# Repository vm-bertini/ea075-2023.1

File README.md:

# EA075 - Introdução a Projeto de Sistemas Embarcados

1° Semestre de 2023

Profa. Paula Dornhofer Paro Costa

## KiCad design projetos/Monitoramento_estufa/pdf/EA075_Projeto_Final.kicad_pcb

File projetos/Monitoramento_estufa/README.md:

# `<Monitoramento_Estufa>`
# `<Greenhouse_monitoring>`

## Apresentação

O presente projeto foi originado no contexto das atividades da disciplina de graduação *EA075 - Sistemas Embarcados*, 
oferecida no primeiro semestre de 2023, na Unicamp, sob supervisão da Profa. Dra. Paula Dornhofer Paro Costa, do Departamento de Engenharia de Computação e Automação (DCA) da Faculdade de Engenharia Elétrica e de Computação (FEEC).

> |Nome  | RA | Curso|
> |--|--|--|
> | Felipe Souza Sisnando de Araujo  | 239617  | Eng. Elétrica|
> | Levi Santos Volotão  | 239783  | Eng. Elétrica|

## Descrição do Projeto
> 
> Hoje em dia, observa-se o surgimento de cada vez mais estufas controladas, pois são um ambiente controlado em que plantações podem ser monitoradas e os aspectos físicos do ambiente podem ser configurados e otimizados para o crescimento e desenvolvimento adequado de uma certa espécie. Embora o custo inicial de uma estufa seja elevado, ela possibilita uma melhora na qualidade dos produtos, aumentando seu valor agregado, e uma dependência menor de características que não podemos controlar quando cultivadas a céu aberto.
> 
> Com uma plantação em estufa, os parâmetros externos não terão tanta influência, e as épocas do ano influenciarão menos as colheitas, garantindo a produção durante o ano todo, reduzindo fenômenos como falta de abastecimento em determinados períodos do ano e prejuízos econômicos dos cultivadores devido ao clima. Como exemplo, observa-se que "no verão, as chuvas demasiadas danificam as plantas e criam condições favoráveis para o aparecimento de doenças, atrapalhando a produção, sendo a época de maiores preços dos produtos hortícolas pela falta de oferta para abastecimento. Por outro lado, o frio e os ventos, do inverno prolongam o ciclo dessas culturas, que consequentemente desprogramam a produção e causam grandes prejuízos econômicos" [Miura, 2011]. Porém, mesmo com influências externas reduzidas, ainda é necessário o controle interno, devido a problemas como a alta irradiação externa resultando em um efeito de aquecimento dentro da estufa,podendo ser prejudicial à plantação caso não ocorra o controle da temperatura necessário. "Além disso, a alta umidade relativa do ar favorece o aparecimento de doenças e provoca menor desenvolvimento das plantas devido ao fato da planta transpirar menos e ter uma menor absorção de nutrientes nessas condições, enquanto, a baixa umidade relativa do ar juntamente com altas temperaturas provoca o aumento da transpiração, fechamento dos estômatos, redução da taxa de transpiração e abortamento das flores devido a uma polinização deficiente" [Lopes e Stripari, 1997]. 
>
> Desse modo, nós propomos o desenvolvimento de um sistema embarcado responsável pelo monitoramento da estufa, que será capaz de identificar quando os valores de temperatura, umidade e luminosidade estiverem fora da faixa desejada, e será capaz de corrigir esses valores, utilizando sistemas de aquecimento e refrigeração (coolers), sistema de ventilação, aspersores de água e um sistema que controla as lâmpadas responsáveis pela luminosidade da estufa, bem como a luminosidade que entra do ambiente externo, a partir de um "shade" (funciona como uma "cortina") cuja abertura é controlada. Esse monitoramento será de grande utilidade para cultivadores de diversos produtos, visto que as faixas de temperautra, luminosidade e umidade desejadas podem ser configuradas conforme os parâmetros adequados para cada espécie. A instalação desse sistema irá aumentar o valor agregado dos seus produtos, viabilizar o cultivo em todas as épocas do ano e permitir um controle automatizado, sem necessidade de mão de obra.
>  

## Descrição Funcional

### Funcionalidades
>O nosso sistema embarcado será capaz de obter a temperatura do ambiente, a luminosidade e a umidade do ar a partir de sensores. Ele mostrará esses valores em um LCD (Liquid Crystal Display). Inicialmente ele amostrará os valores de temperatura e umidade a cada 10 minutos e a luminosidade a cada 5 minutos, porém esses parâmetros serão configuráveis, e a frequência de amostragem de cada fator pode ser alterada conforme a necessidade do cliente. O sistema também será capaz de detectar quando um valor estiver fora da faixa adequada configurada, e para esse caso, irá iniciar rotinas de tratamento adequadas, controlando o funcionamento dos aspersores de água, sistema de aquecimento, coolers, lâmpadas e "shade".
>
> O sistema poderá : 
> - Ligar e desligar os aspersores de água
>
> - Ligar, desligar e controlar a temperatura do sistema de aquecimento
>
> - Ligar, desligar e controlar a temperatura dos coolers
> 
> - Movimentar o "shade" : Abrir o shade caso a luminosidade esteja abaixo da desejada e fechar o shade caso esteja acima da desejada
>
> - Ligar, desligar e controlar a intensidade da luz das lâmpadas de LED (as lâmpadas serão utilizadas caso a luminosidade não seja o bastante mesmo com o shade totalmente aberto (por exemplo à noite)).

### Configurabilidade
> A estufa está sendo projetada para uma diversidade de espécies de plantas, e cada planta tem suas especificidades em relação ao ambiente para ter uma produtividade melhor. Portanto, será possível configurar a faixa de valores desejada e a frequência com que os dados serão amostrados. Essa configuração será feita por botões. O LCD no modo exibição mostrará o último estado amostrado, e atualizará a cada amostragem. Ao apertar o botão de configuração, o sistema irá funcionar no modo de configuração, e o LCD mostrará os valores definidos para o período de amostragem e os valores máximo e mínimo para cada parâmetro. Para mudar esses valores, haverá 3 botões (além do botão que muda entre o modo de exibição e configuração, totalizando 4 botões), um botão que muda a característica cujo valor deseja-se alterar, um botão para incrementar esse valor e um botão para decrementar esse valor. Ao pressionar o botão de configuração novamente, retorna-se para o modo de exibição. Os valores possíveis para as características obedecerão a limites de acordo com as especificações dos sensores, e o período de amostragem poderá variar de 1 a 59 minutos.
### Eventos
>  O sistema deve tratar os seguintes eventos periódicos:
>
> - Amostragem de temperatura: De X em X minutos deve-se obter o valor da temperatura lido no sensor (em que X é um valor configurável, inicialmete colocado como 10 minutos) 
>
> - Amostragem de umidade: De Y em Y minutos deve-se obter o valor da umidade lido no sensor (em que Y é um valor configurável, inicialmete colocado como 10 minutos) 
>
> - Amostragem de luminosidade: De Z em Z minutos deve-se obter o valor da umidade lido no sensor (em que Z é um valor configurável, inicialmete colocado como 10 minutos)
>
> O sistema deve tratar os seguintes eventos não periódicos:
> 
> - Temperatura dentro da faixa desejada
> 
> - Temperatura abaixo da temperatura mínima configurada
>
> - Temperatura acima da temperatura máxima configurada
>
> - Umidade dentro da faixa desejada
> 
> - Umidade abaixo da umidade mínima configurada
>
> - Umidade acima da umidade máxima configurada
>
> - Luminosidade dentro da faixa desejada
> 
> - Luminosidade abaixo da luminosidade mínima configurada
>
> - Luminosidade acima da luminosidade máxima configurada
>
> - Botão para mudar para o modo configuração apertado
>
> - Botão para incrementar em 1 o valor do parâmetro selecionado apertado
>
> - Botão para decrementar em 1 o valor do parâmetro selecionado apertado
>
> - Botão para mudar parâmetro selecionado (cujo valor deseja-se mudar) apertado
>
>

### Tratamento de Eventos
>
> - Tratamento da amostragem de temperatura: 
> 
> Obter o valor da temperatura e analisar se está acima, abaixo ou dentro da faixa desejada, acionando o tratamento do evento correspondente. 
> 
> - Tratamento da amostragem de umidade:
> 
> Obter o valor da umidade e analisar se está acima, abaixo ou dentro da faixa desejada, acionando o tratamento do evento correspondente. 
> 
> - Tratamento da amostragem de luminosidade: 
> 
>  Obter o valor da luminosidade e analisar se está acima, abaixo ou dentro da faixa desejada, acionando o tratamento do evento correspondente. 
>  
> - Tratamendo quando a temperatura está dentro da faixa desejada:
> 
> O sistema retorna ao fluxo normal do programa
> 
> - Tratamento quando a temperatura está abaixo da temperatura mínima configurada:
> 
> Caso o cooler esteja ligado, desliga o cooler.
> 
>  Caso contrário, se o sistema de aquecimento estiver desligado, liga-se o sistema de aquecimento. Se estiver ligado, aumenta em 5°C a temperatura do aquecedor.
> 
> - Tratamento quando a temperatura está acima da temperatura máxima configurada:
> 
> Caso o aquecedor esteja ligado, desliga o aquecedor. 
> 
> Caso contrário, se o cooler estiver desligado, liga-se o cooler. Se estiver ligado, diminui em 5°C a temperatura do cooler.
> 
> - Tratamento quando a umidade está dentro da faixa desejada:
> 
> O sistema retorna ao fluxo normal do programa
> 
> - Tratamento quando a umidade está abaixo da umidade mínima configurada:
> 
> Caso a ventilação esteja ligada, desliga a ventilação. 
> 
> Caso contrário, liga-se o aspersor de água e, após 30 segundos, ele é desligado.
>
> - Tratamento quando a umidade está acima da umidade máxima configurada:
> 
> Liga-se o sistema de ventilação. 
> 
> Caso já esteja ligado, aumenta sua potência.
>
> - Tratamento quando a luminosidade está dentro da faixa desejada:
> 
> O sistema retorna ao fluxo normal do programa
> 
> - Tratamento quando a luminosidade está abaixo da luminosidade mínima configurada:
> 
> Caso o shade esteja fechado, abrir o shade.
> 
>  Caso contrário, acender as lâmpadas de LED. Se estiverem acesas, aumentar intensidade da luz.
>
> - Tratamento quando a luminosidade está acima da luminosidade máxima configurada:
> 
> Caso as lâmpadas estejam ligadas, desligar as lâmpadas.
> 
>  Caso contrário, fechar o shade
>
> - Tratamento quando o botão de configuração está apertado:
> 
> Caso esteja no modo exibição, muda para o modo de configuração (o LCD passa a mostrar os limites dos parâmetros e o período de amostragem)
> 
> Caso esteja no modo de configuração, muda para o modo exibição(o LCD mostra os valores de temperatura, luminosidade e umidade lidos pelos sensores), estabelece os novos valores limites das faixas de temperatura, umidade e luminosidade e estabelece o novo período de amostragem.
>
> - Tratamento quando o botão de incremento está apertado:
> 
> Caso esteja no modo configuração, aumenta o valor da característica selecionada em 1
> 
> Caso esteja no modo exibição, esse evento é ignorado e o programa continua seu fluxo normal
> 
> - Tratamento quando o botão de decremento está apertado:
> 
> Caso esteja no modo configuração, decrementa o valor da característica selecionada em 1
> 
> Caso esteja no modo exibição, esse evento é ignorado e o programa continua seu fluxo normal
>
> - Tratamento quando o botão para mudar parâmetro selecionado está apertado:
> 
> Caso esteja no modo configuração, muda a característica selecionada
> 
> Caso esteja no modo exibição, esse evento é ignorado e o programa continua seu fluxo normal
>

## Descrição Estrutural do Sistema

>
>
> Observa-se que podem-se destacar três grandes blocos funcionais: o microcontrolador, os sensores e os atuadores. No bloco dos sensores tem-se os sensores de luminosidade, umidade e temperatura, bem como os botões (que podem ser considerados como sensores de pressão); já como atuadores, observa-se o cooler, shade,  sistema de ventilação, aquecedor, lâmpadas e os aspersores, bem como o LCD (que pode ser considerado um atuador, permitindo a visualização de dados na tela). Os sensores são capazes de transformar parâmetros físicos em sinais elétricos, que podem ser processados pelo microcoontrolador. A partir desses sinais, o microcoontrolador processa o programa de tratamento de enventos (conforme explicado em seções anteriores),  e envia sinais de controle para os atuadores, que atuam com base nesses sinais e transformam esses sinais elétricos em alguns parâmetros físicos, permitindo o correto funcionamento do circuito.

## Referências
> http://sistemaolimpo.org/midias/uploads/fa4a7bc53246a8a9bf8642442a68fe3c.pdf
>
> https://www.horticeres.com.br/noticias/dicas-para-cultivo-protegido/#:~:text=Para%20efeito%20estufa%20(regi%C3%B5es%20muito,aproximadamente%20400%20a%201000%20m%C2%B2.
>
>https://www.rijkzwaan.com.br/blog/estufa-ou-guarda-chuva
>
>Miura, M. (2011). Análise Econômica do Cultivo em Ambiente Protegido.
>
>https://www.zanatta.com.br/cultivo-protegido/
>
>https://embarcados.com.br/sensores-e-atuadores-iot/

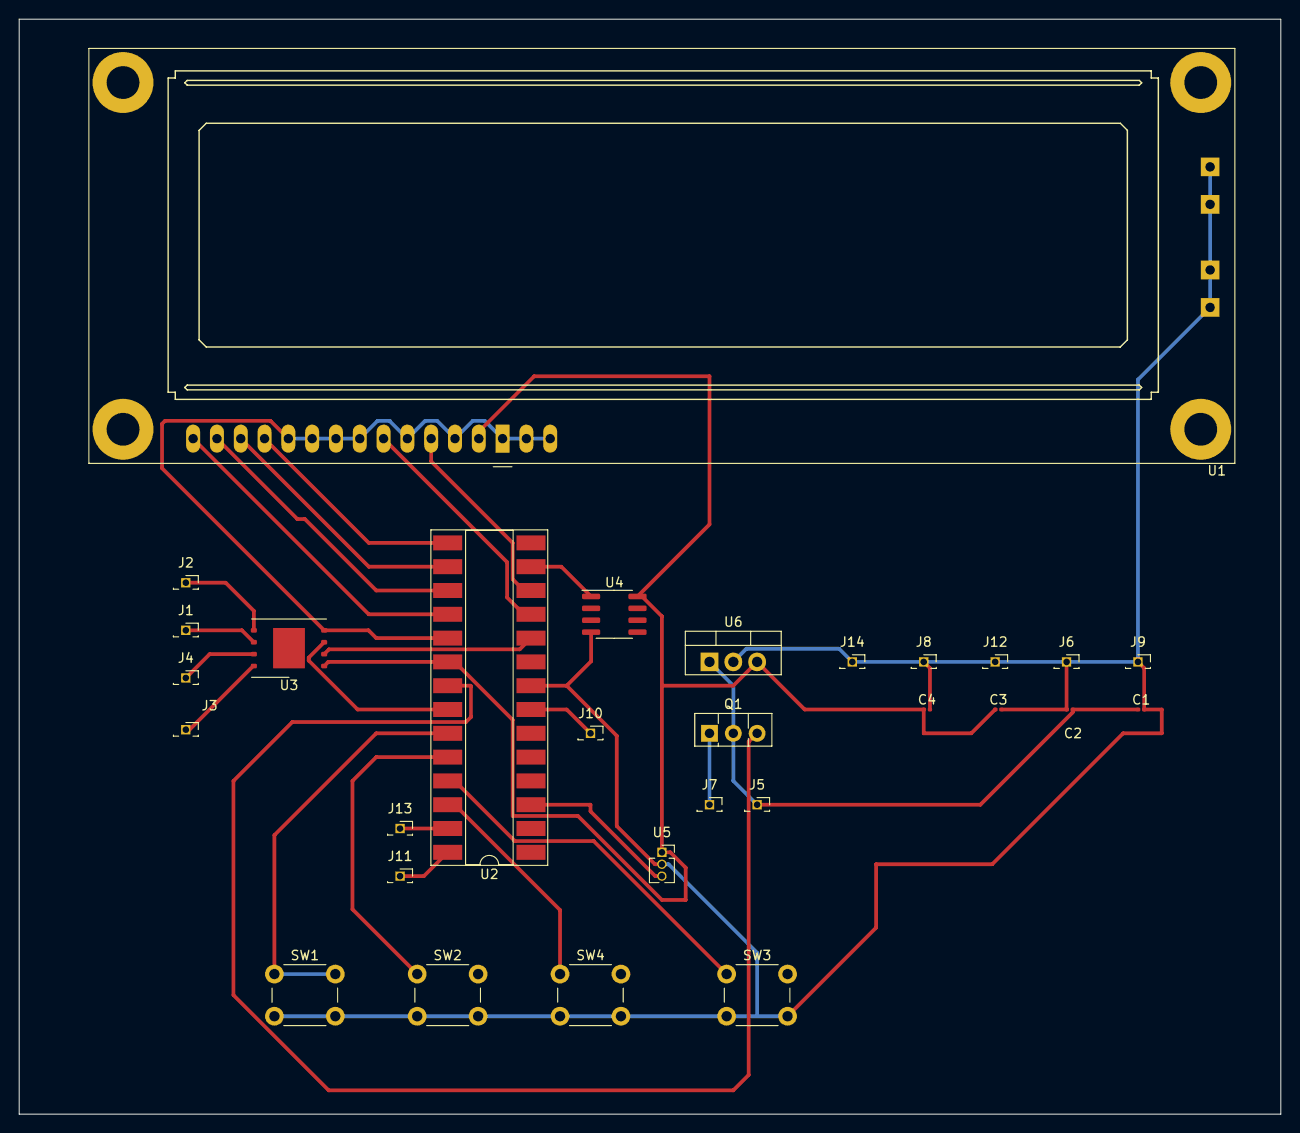
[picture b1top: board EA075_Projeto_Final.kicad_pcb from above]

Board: 2 copper layers, 134.6 x 116.8 mm, 29 parts (0 on the bottom side), 26 nets.

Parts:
C1: 470uf; C_0201_0603Metric
C2, C3: 0.1uf; C_0201_0603Metric
C4: 220uf; C_0201_0603Metric
J1: 110V; PinSocket_1x01_P1.27mm_Vertical
J2: GNDAC; PinSocket_1x01_P1.27mm_Vertical
J3: Lampada-; PinSocket_1x01_P1.27mm_Vertical
J4: Lampada+; PinSocket_1x01_P1.27mm_Vertical
J5: 12V; PinSocket_1x01_P1.27mm_Vertical
J6: GND; PinSocket_1x01_P1.27mm_Vertical
J7: Motor+; PinSocket_1x01_P1.27mm_Vertical
J8: Motor-; PinSocket_1x01_P1.27mm_Vertical
J9: Cooler-; PinSocket_1x01_P1.27mm_Vertical
J10: Cooler+; PinSocket_1x01_P1.27mm_Vertical
J11: Heater+; PinSocket_1x01_P1.27mm_Vertical
J12: Heater-; PinSocket_1x01_P1.27mm_Vertical
J13: luminosidade+; PinSocket_1x01_P1.27mm_Vertical
J14: luminosidade-; PinSocket_1x01_P1.27mm_Vertical
Q1: BD135; TO-126-3_Vertical
SW1, SW2, SW3, SW4: SW_Push; SW_PUSH_6mm
U1: LCD-016N002L
U2: PIC16F886-IP; DIP-28_W8.89mm_SMDSocket_LongPads
U3: WSON-8-1EP_8x6mm_P1.27mm_EP3.4x4.3mm
U4: LM35-D; SOIC-8_3.9x4.9mm_P1.27mm
U5: PinSocket_1x03_P1.27mm_Vertical
U6: LM7805_TO220; TO-220-3_Vertical

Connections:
+12V: C1.1, C2.1, J5.1, Q1.2 (C), U6.1 (VI)
GND: C1.2, C2.2, C3.2, C4.2, J6.1, J8.1, J9.1, J12.1, J14.1, SW1.2, SW2.2, SW3.2, SW4.2, U1.1 (VSS), U1.3 (VO), U1.5 (R/~W), U1.7 (DB0), U1.8 (DB1), U1.9 (DB2), U1.10 (DB3), U1.15 (A/VEE), U1.16 (K), U1.A1, U1.A2, U1.K1, U1.K2, U2.8 (VSS), U2.19 (VSS), U3.4 (GND), U4.4 (GND), U5.2 (GND), U6.2 (GND)
unnamed: J1.1, U3.6 (AC_IN+)
unnamed: J2.1, U3.5 (AC_IN-)
unnamed: J3.1, U3.8 (AC_LOAD-)
unnamed: J4.1, U3.7 (AC_LOAD+)
unnamed: J7.1, Q1.1 (E)
unnamed: J10.1, U2.7 (~SS/C2OUT/AN4/RA5)
unnamed: J11.1, U2.28 (ICSPDAT/RB7)
unnamed: J13.1, U2.27 (ICSPCLK/RB6)
unnamed: Q1.3 (B), U2.21 (INT/AN12/RB0)
unnamed: U1.11 (DB4), U2.15 (RC4/SDI/SDA)
unnamed: U1.12 (DB5), U2.16 (RC5/SDO)
unnamed: U1.13 (DB6), U2.17 (RC6/TX/CK)
unnamed: U1.14 (DB7), U2.18 (RC7/RX/DT)
unnamed: U1.6 (E), U2.11 (RC0/T1OSO/T1CK1)
unnamed: U1.4 (RS), U2.12 (RC1/T1OSI/CCP2)
unnamed: C3.1, C4.1, U1.2 (VDD), U2.20 (VDD), U3.1 (VCC), U4.8 (+V_{S}), U5.1 (vcc), U6.3 (VO)
unnamed: U2.3 (C12IN1-/AN1/RA1), U5.3 (Analog)
unnamed: U2.10 (CLKOUT/OSC2/RA6), U3.2 (ZC)
unnamed: SW1.1, U2.23 (P1B/AN8/RB2)
unnamed: U2.22 (P1C/AN10/RB1), U3.3 (DIM)
unnamed: SW3.1, U2.25 (P1D/AN11/RB4)
unnamed: SW2.1, U2.24 (PGM/C12IN2-/AN8/RB3)
unnamed: U2.13 (RC2/P1A/CCP1), U4.1 (V_{OUT})
unnamed: SW4.1, U2.26 (~T1G/AN13/RB5)

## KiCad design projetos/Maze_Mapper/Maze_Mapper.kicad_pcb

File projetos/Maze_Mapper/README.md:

# `<Mapeador de Labirinto>`
# `<Maze Mapper>`

## Apresentação

O presente projeto foi originado no contexto das atividades da disciplina de graduação *EA075 - Sistemas Embarcados*, 
oferecida no segundo semestre de 2022, na Unicamp, sob supervisão da Profa. Dra. Paula Dornhofer Paro Costa, do Departamento de Engenharia de Computação e Automação (DCA) da Faculdade de Engenharia Elétrica e de Computação (FEEC).

> |Nome  | RA | Curso|
> |--|--|--|
> | Caio Mendes Rehder  | 232607  | Eng. Elétrica|
> | Daniel Yamamoto Damico  | 220770  | Eng. Elétrica|

## Descrição do Projeto
> O projeto “Maze mapper” visa facilitar o mapeamento de estruturas de caminhos ramificados, como labirintos, encanamentos e túneis, que são de difícil acesso humano. Embora esse projeto tenha o objetivo de ser um protótipo que funcione apenas em ambientes mais controlados, a solução proposta, se aplicada com as devidas modificações circunstanciais, teria utilidade em uma ampla variedade de setores, incluindo manutenção de infraestrutura e inspeção de segurança.
> Em um caso de tubulações, por exemplo, seria possível tornar o trabalho humano mais simples e eficiente, evitando danos desnecessários, como abrir encanamentos em vários pontos para encontrar obstruções, e acelerando o processo de mapeamento.
> A solução baseia-se em um sistema embarcado de mapeamento quase inteiramente autônomo que usa tecnologias de sensores e mapeamento bidimensional para navegar e mapear essas estruturas complexas. O sistema visa ser capaz de detectar pontos de obstrução, saídas e ramificações, bem como registrá-los em um mapa que preserve as características espaciais do ambiente avaliado.
> Uma característica distinta do sistema seria sua capacidade de salvar o progresso em uma memória externa por meio de conexão USB, de modo a diminuir a necessidade de memória não-volátil no sistema, o que possibilitaria uma redução de custos.
> Assim, com seu potencial para simplificar o mapeamento de estruturas complexas e reduzir o tempo e os custos associados a essas tarefas, espera-se que o sistema desenvolvido para esse projeto possa ser adotado em muitas aplicações subsequentes de cunho similar.

## Descrição Funcional

### Funcionalidades
> O projeto possui uma série de funcionalidades para realizar a tarefa proposta, conforme as descrições a seguir.

> Seu sistema emprega sensores para identificar os possíveis caminhos a serem seguidos e, com base nessas informações, toma a decisão de qual caminho seguir quando diante de uma ramificação, a fim de evitar repetições desnecessárias e otimizar o tempo de mapeamento.

> Para a locomoção, o dispositivo conta com a funcionalidade de ir para frente, para trás e rotacionar até 180º para ambos os lados de acordo com instruções automatizadas.

> O sistema também realiza a função de identificar obstruções, ramificações e saídas e registrá-las como pontos chave do mapeamento. Paralelamente, há o monitoramento da distância atual em relação ao ponto inicial para que o dispositivo não vá além de um raio de atuação máximo estabelecido para o sistema.
Para garantir que todas as informações sejam armazenadas e que o progresso do mapeamento não seja perdido, o sistema periodicamente salva o mapeamento realizado em uma memória externa. 

> Além disso, o sistema inclui um alerta que é acionado para um controlador externo caso o dispositivo fique preso, o que, por agilizar a comunicação, colabora para contornar situações de interrupção inesperada. Ademais, após o disparo desse alerta, o sistema automaticamente interrompe todas as suas funcionalidades exceto o acendimento de lâmpadas externas de sinalização, aumentando a chance de recuperação do equipamento. 

> O dispositivo também será capaz de receber um sinal de retorno imediato do controlador externo, situação na qual todas as funcionalidades de mapeamento são interrompidas e o dispositivo automaticamente navega de volta ao ponto inicial.

### Configurabilidade
> O sistema disporá de 4 modos configuráveis por meio de dois switches. Um dos switches regulará se o objeto de busca do sistema são obstruções (caminhos sem saída) ou saídas (pontos onde é possível sair do labirinto). Já o segundo, configura se serão buscados apenas uma obstrução ou saída ou se serão mapeados múltiplos objetos de busca, de forma que, no primeiro caso, o sistema automaticamente retorna para o ponto inicial ao encontrar o primeiro objeto de busca e no segundo, apenas interrompe sua operação se for comandado externamente ou se ficar preso.
Com isso, os 4 modos configuráveis são:
- Uma obstrução
- Múltiplas obstruções
- Uma saída
- Múltiplas saídas

### Eventos
> Periódicos

1. Verificação do sensor frontal (500ms).
2. Verificar status da locomoção (15000ms).

> Não Periódicos (não ocorrem simultaneamente, portanto não preocupações com tempo mínimo)

1. Mapeamento.
2. Verificação de bateria.
3. Requisição de retorno.
4. Verificar a distância do ponto inicial.
5. Controle de Navegação.
6. Encontrou ramificação.
7. Encontrou obstrução.
8. Encontrou saída.
9. Liga/desliga.

### Tratamento de Eventos
> Periódicos:

1. Verifica se é necessário mapear uma nova posição com base na distância percorrida desde a última atualização.
2. Caso a locomoção seja comprometida, enviar sinal de ajuda e a última posição registrada (localização atual).

> Não Periódicos

1. Paraliza o motor, marca a nova posição, categoriza-a, e volta a ligar o motor quando todo o processamento necessário para prosseguir é realizado. É trigger dos eventos não periódicos de 2 a 5.
2. Caso a bateria esteja abaixo de um certo limite, configura o carrinho para voltar ao ponto inicial.
3. Interromper o processamento normal e configurar o carrinho para retornar ao ponto inicial.
4. Se a distância for maior que o raio de atuação, dar meia volta.
5. Com base no tipo de ponto (ramificação, obstrução, saída, etc) em que se está, corrige a orientação do carrinho para que este possa continuar se movimentando para frente. É trigger dos eventos não-periódicos de 6 a 8, dependendo do tipo de ponto.
6. Salvar ponto de ramificação no mapa e escolher por qual caminho seguir a partir da posição atual.
7. Salvar ponto como obstrução e dar meia volta. Caso em modo de busca por obstrução única, retornar ao ponto de início (tarefa concluída).
8. Salvar ponto como saída e dar meia volta. Caso em modo de busca por saída única, retornar ao ponto de início (tarefa concluída).
9. Ligar e desligar o sistema.

## Descrição Estrutural do Sistema
A estrutura necessária ao desenvolvimento do projeto pode ser sintetizada por meio do diagrama de blocos abaixo:

### Descrição dos blocos:
#### SENSORES: 
> Descrição: Contempla o conjunto de sensores necessários para que o sistema obtenha informações do mundo externo, como a posição atual, direção de movimento e se há algo nas proximidades do dispositivo que exige a chamada de um evento

> Relações com outros blocos:
> > Tem como fonte de alimentação o bloco BATERIA
> 
> > Envia informações e sinalizadores de evento ao MICROCONTROLADOR 

#### MICROCONTROLADOR:
> Descrição: Centro de processamento do sistema embarcado, o qual realiza todas as tarefas relacionados ao tratamento de dados e eventos, além do envio de dados e sinais de controle aos demais blocos

> Relações com outros blocos:
> > Alimentado pela BATERIA
> 
> > Envia sinais de controle para os blocos BATERIA, SISTEMA MEC NICO e SISTEMA Rx/Tx
> 
> > Envia dados para MEMÓRIA EXTERNA  
> 
> > Recebe sinais e dados dos blocos SENSOR e SISTEMA Rx/Tx durante a execução do programa e recebe configurações do bloco SWITCH antes da execução

#### MEMÓRIA EXTERNA:
> Descrição: Bloco responsável por armazenar permanentemente os dados de mapeamento obtidos ao longo da navegação, conectado ao microcontrolador por uma entrada USB

> Relações com outros blocos:
> > Alimentado pela BATERIA
> 
> > Apenas recebe dados do bloco MICROCONTROLADOR 

#### SISTEMA Rx/Tx (RECEPÇÃO E TRANSMISSÃO):
> Descrição: Sistema responsável pela comunicação entre o usuário e o dispositivo principal, utilizado apenas para encerrar a operação, seja por requisição do usuário (recepção do sinal de retorno) ou pelo dispositivo quando este se encontrar impossibilitado de retornar (transmissão de sinal de “socorro”)

> Relações com outros blocos: 
> > Alimentado pela BATERIA
> 
> > Comunica-se com o CONTROLE EXTERNO e com o MICROCONTROLADOR  por meio da transmissão e recepção de sinais 

#### SISTEMA MECANICO:
> Descrição: Toda a estrutura mecânica de motor, rodas e outros componentes necessários para que o dispositivo se mova segundo os comandos do microcontrolador

> Relações com outros blocos:
> > Alimentado pela BATERIA
> 
> > Recebe sinais de controle apenas do MICROCONTROLADOR 

#### BATERIA:
> Descrição: Fonte de energia elétrica de todo o sistema embarcado

> Relações com outros blocos:
> > Relaciona-se com todos os demais blocos, exceto MEMÓRIA EXTERNA e CONTROLE EXTERNO, alimentando-os com energia elétrica

#### SWITCH (Botões e Switches):
> Descrição: Componentes responsáveis por ligar e desligar o aparelho (um botão simples) e por selecionar o modo de atuação a ser configurado (dois switches)

> Relações com outros blocos:
> > Envia sinais de controle à BATERIA e ao MICROCONTROLADOR 

#### CONTROLE EXTERNO:
> Descrição: Dispositivo não integrado fisicamente ao sistema principal e que permanecerá com o usuário a todo momento, tendo como únicas funções enviar um sinal para que o aparelho retorne e receber o sinal de “socorro” indicando que o aparelho não consegue voltar

> Relações com outros blocos:
> > Apenas se comunica com o bloco SISTEMA Rx/Tx

## Especificações

### Especificação Estrutural

https://docs.google.com/document/d/1n6RbynMdM-dFheosjJLS--sK0qMWMoK55iLZcWa1GU8/edit?usp=sharing

### Especificação de Algoritmos

https://docs.google.com/document/d/1WOtS1sczeaAlzp9vi0PXV7JNHWrlSyEX5yq-FA1AXzs/edit?usp=sharing

## Referências
- https://www.youtube.com/playlist?list=PLifLftIJFUm-1iIAEPWvuSJTA50YKYD7J
- megaAVR® Data Sheet, ATmega48A/PA/88A/PA/168A/PA/328/P
- Módulo Sensor de Distancia Ultrassónico, Chipsce, Hc-Sr04

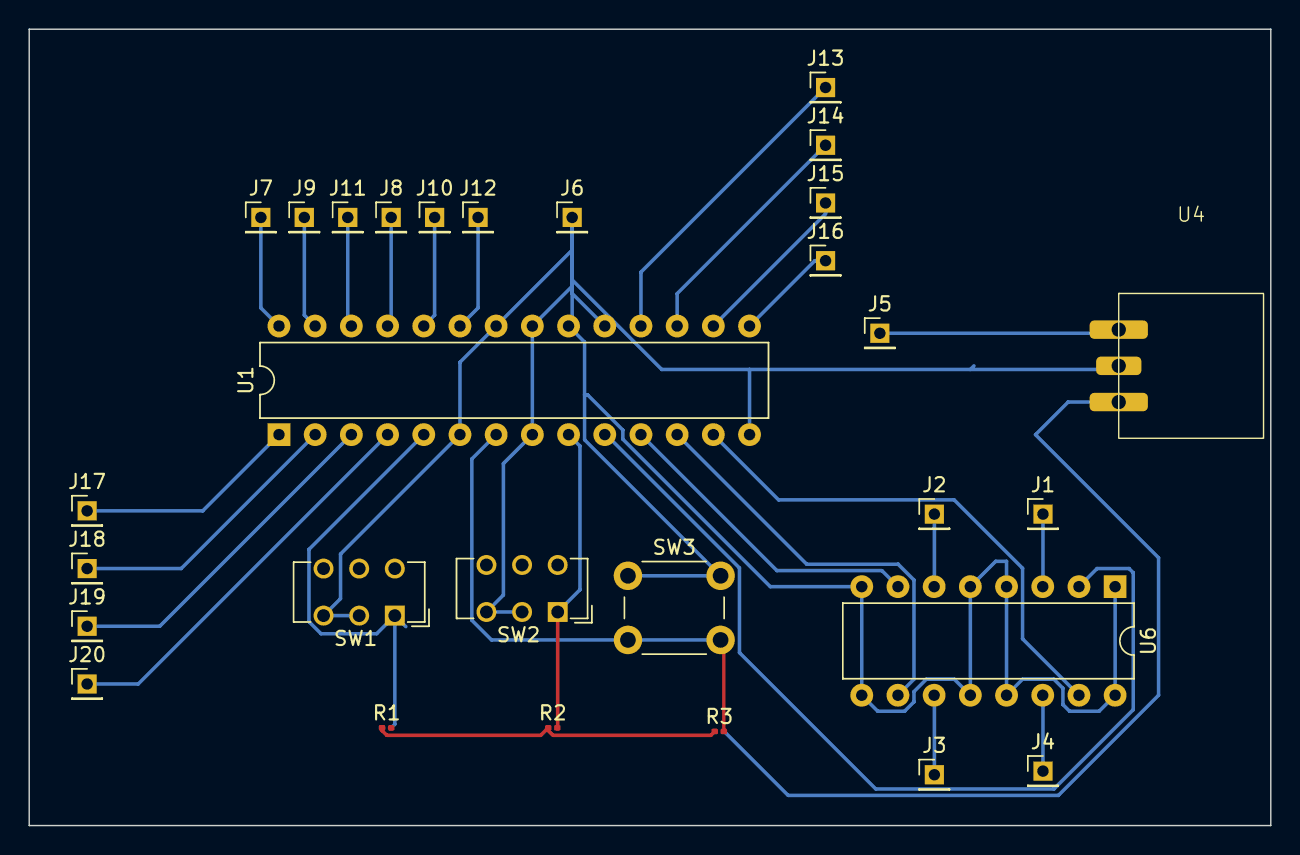
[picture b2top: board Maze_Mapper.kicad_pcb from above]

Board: 2 copper layers, 87.1 x 55.9 mm, 29 parts (0 on the bottom side), 28 nets.

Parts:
J1, J2, J3, J4, J6, J7, J8, J9, J10, J11, J12, J13, J14, J15, J16, J17, J18, J19, J20: Conn_01x01_Pin; PinHeader_1x01_P2.00mm_Vertical
J5: Conn_01x01_Socket; PinHeader_1x01_P2.00mm_Vertical
R1, R2, R3: R; R_0201_0603Metric
SW1, SW2: SW_Push_SPDT; SW_CuK_JS202011CQN_DPDT_Straight
SW3: SW_Push; SW_PUSH_6mm
U1: ATmega328-P; DIP-28_W7.62mm
U4: 5V_regulator
U6: L293D; DIP-16_W7.62mm

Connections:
5V: R1.1, R2.1, R3.1
+10V: J5.1, U4.1 (In)
GND: J6.1, SW1.2 (B), SW1.3 (C), SW2.2 (B), SW2.3 (C), SW3.1, U1.6 (PD4), U1.8 (GND), U1.14 (PB0), U1.19 (PB5), U1.20 (AVCC), U1.21 (AREF), U1.22 (GND), U4.2 (GND), U6.1 (EN1,2), U6.4 (GND), U6.5 (GND), U6.8 (VCC2), U6.9 (EN3,4), U6.12 (GND), U6.13 (GND), U6.16 (VCC1)
unnamed: J1.1, U6.3 (1Y)
unnamed: J2.1, U6.6 (2Y)
unnamed: J3.1, U6.11 (3Y)
unnamed: J4.1, U6.14 (4Y)
PB1: J16.1, U1.15 (PB1)
PB2: J15.1, U1.16 (PB2)
PB3: J14.1, U1.17 (PB3)
PB4: J13.1, U1.18 (PB4)
PB6: R2.2, SW2.1 (A), U1.9 (XTAL1/PB6)
PB7: U1.10 (XTAL2/PB7), U6.2 (1A)
PC0: J12.1, U1.23 (PC0)
PC1: J10.1, U1.24 (PC1)
PC2: J8.1, U1.25 (PC2)
PC3: J11.1, U1.26 (PC3)
PC4: J9.1, U1.27 (PC4)
PC5: J7.1, U1.28 (PC5)
PC6: J17.1, U1.1 (~RESET/PC6)
PD0: J18.1, U1.2 (PD0)
PD1: J19.1, U1.3 (PD1)
PD2: J20.1, U1.4 (PD2)
PD3: R1.2, SW1.1 (A), U1.5 (PD3)
PD5: U1.11 (PD5), U6.7 (2A)
PD6: U1.12 (PD6), U6.10 (3A)
PD7: U1.13 (PD7), U6.15 (4A)
VCC: R3.2, SW3.2, U1.7 (VCC)

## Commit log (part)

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2023-05-22 Update readme.md
    Arrumando problemas de link com draw.io
2023-05-22 Images
2023-05-22 Update README.md
    Images
2023-05-22 Update README.md
    Images 2
2023-05-22 Update README.md
    Images3
2023-05-29 Rename ea075-E2.md to README.md
2023-06-15 Rename components.m to components.md
2023-06-21 adicionado pastas com arquivo placeholder e renomeado pasta de datasheets
2023-06-21 adicionado TODO's ao README
2023-06-22 Create gerber
2023-06-22 Create pdf
2023-06-22 Create images
2023-06-22 Create src_zip
2023-06-23 Create datsheets
2023-06-23 Create links
2023-06-23 Create arquivos
2023-06-23 atualizado descrição do projeto
2023-06-23 funcionalidades: nada alterado
2023-06-23 Descriçao estrutural do sistema mudado de lugar, especificação estrutural modificada
2023-06-23 Descriçao estrutural do sistema mudado de lugar, especificação estrutural modificada2
2023-06-23 ajuste de titulos
2023-06-24 spec do algoritmo
2023-06-24 fix no grafico mermaid do algoritmo
2023-06-24 fix no fluxograma do algoritmo
2023-06-24 Update readme.md
    Atualizando read.me.
    Removendo os comentários
2023-06-24 Update readme.md
    Ajustando defeitos de formatação
2023-06-24 Update readme.md
    Ajustando outros erros de formatação
2023-06-24 criar folder 3d_models
2023-06-24 Adicionadas as visões 3D da placa
2023-06-24 add gerber files
2023-06-24 Add pd with sch view
2023-06-24 Add pdf with pcb view
2023-06-24 Add zip file
2023-06-25 Create components.md
    Adicionando components file
2023-06-25 Update components.md
    Adicionando conteúdo a components.md
2023-06-25 Create gerber folder
2023-06-25 adding gerber files
2023-06-25 adding pdf file
2023-06-25 Adding images
2023-06-25 adding src.zip file
2023-06-25 Update and rename src_zip to src_zip.md
    Adicionando intruções simples para abrir projeto
2023-06-25 Update readme.md
    v1.0.0
2023-06-25 Create a
2023-06-25 Fixing pdf
2023-06-25 Update readme.md
    Read me Arquivos importantes
2023-06-25 add gerber
2023-06-25 add images
2023-06-25 add pdfs
2023-06-25 update components
2023-06-25 update src zip file
2023-06-25 atualizado secao de arquivos importantes
2023-06-25 corrigido descricao estrutural do sistema
2023-06-25 Create 1
2023-06-26 Create i
2023-06-26 3 entrega
2023-06-26 3 entrega.1
2023-06-26 Revert "2023.1_EA075_E3"
2023-06-26 Revert "Entrega 3 - Padronizador variável de linha de produção"
2023-06-27 Create x
2023-06-27 ordenacao correta
2023-06-29 Revert "EA075-EntregaFinal"
2023-06-30 Revert "Revert "Entrega 3 - Padronizador variável de linha de produção""
